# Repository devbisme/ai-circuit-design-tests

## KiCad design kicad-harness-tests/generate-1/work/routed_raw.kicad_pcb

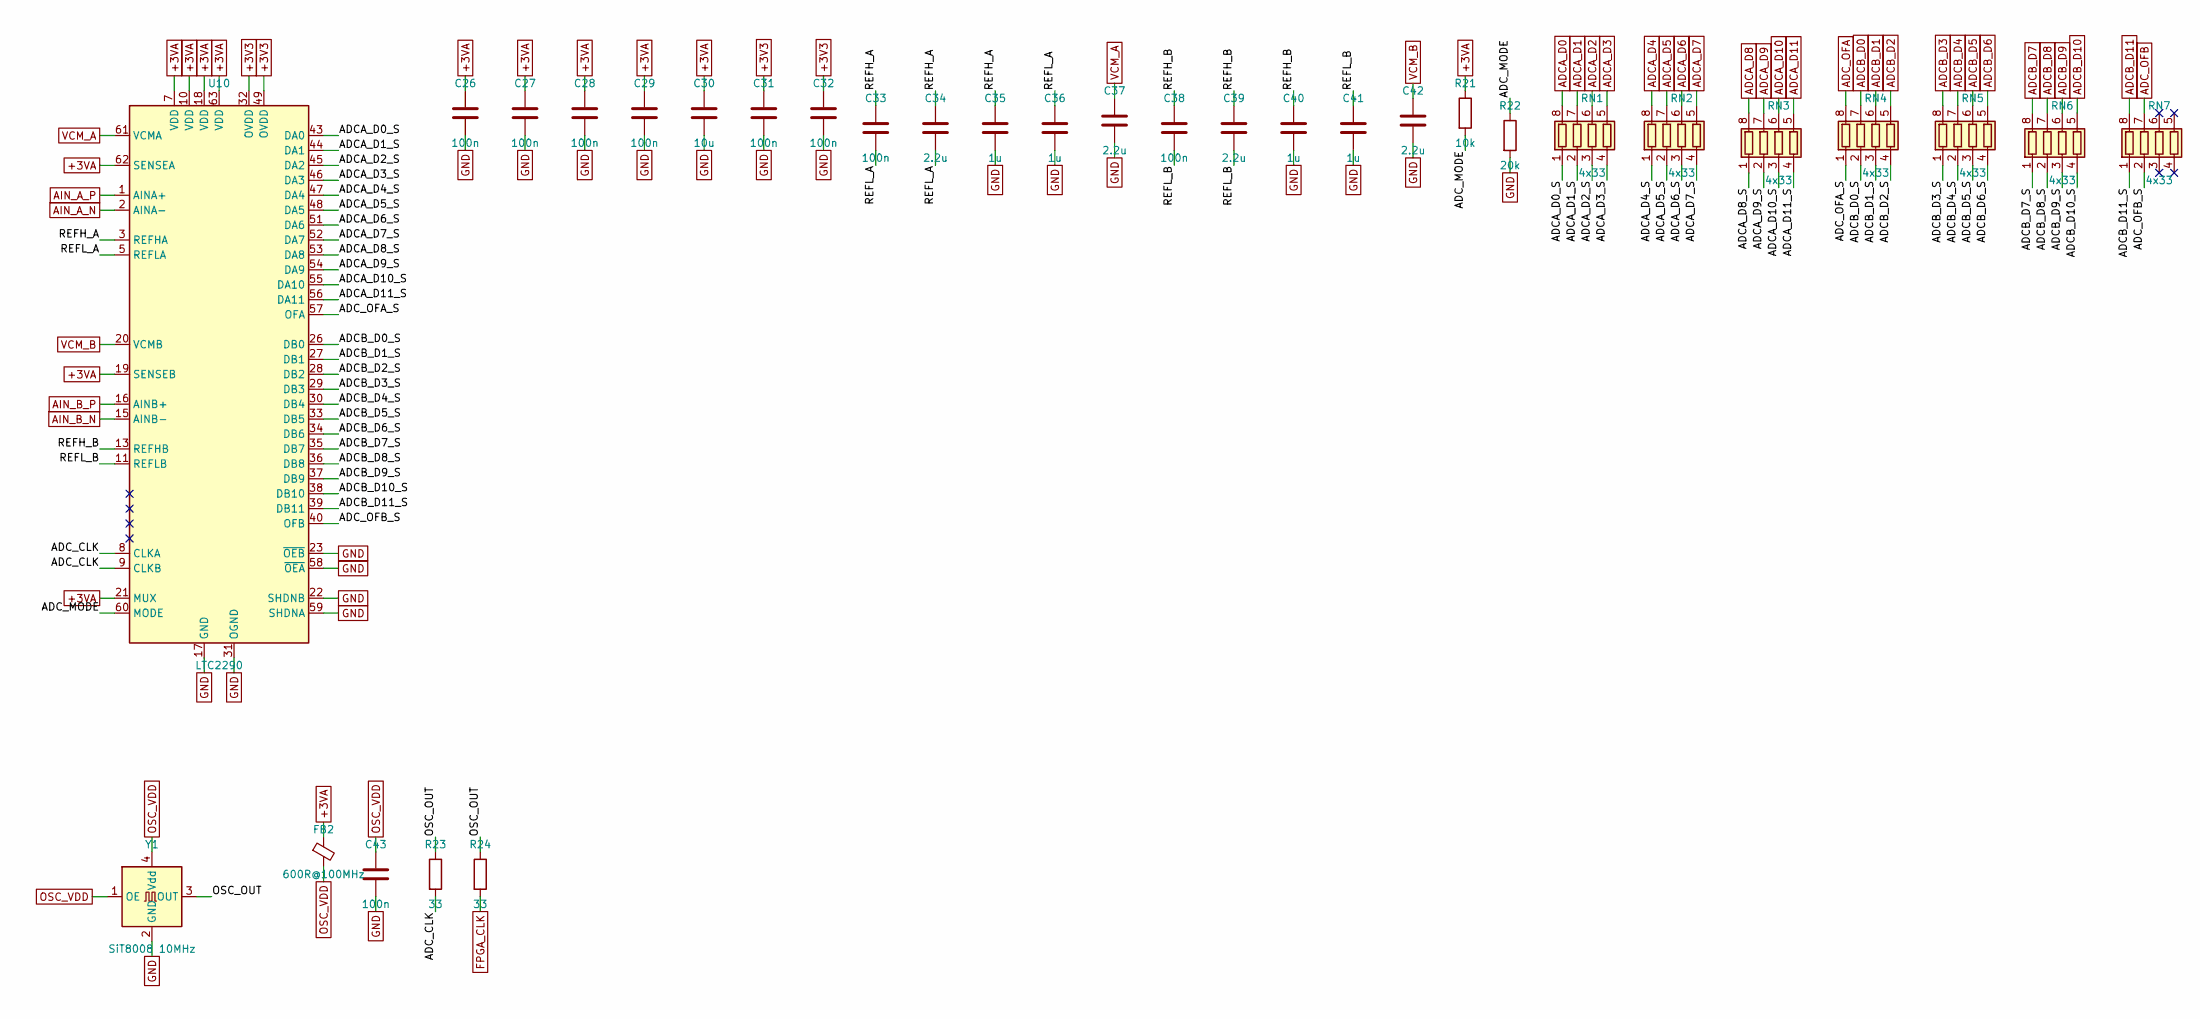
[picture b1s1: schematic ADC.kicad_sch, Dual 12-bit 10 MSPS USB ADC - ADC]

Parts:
C26, C27, C28, C29, C31, C32, C33, C38, C43: 100n; C_0603_1608Metric
C30: 10u; C_0805_2012Metric
C34, C37, C39, C42: 2.2u; C_0603_1608Metric
C35, C36, C40, C41: 1u; C_0603_1608Metric
FB2: 600R@100MHz; L_0805_2012Metric
R21: 10k; R_0603_1608Metric
R22: 20k; R_0603_1608Metric
R23, R24: 33; R_0603_1608Metric
RN1, RN2, RN3, RN4, RN5, RN6, RN7: 4x33; R_Array_Convex_4x0603
U10: LTC2290; QFN-64-1EP_9x9mm_P0.5mm_EP7.15x7.15mm
Y1: SiT8008 10MHz; Oscillator_SMD_SiT_PQFN-4Pin_3.2x2.5mm

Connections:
+3V3: C31.1, C32.1, U10.32 (OVDD), U10.49 (OVDD); also elsewhere on the board
+3VA: C26.1, C27.1, C28.1, C29.1, C30.1, FB2.1, R21.1, U10.7 (VDD), U10.10 (VDD), U10.18 (VDD), U10.19 (SENSEB), U10.21 (MUX), U10.62 (SENSEA), U10.63 (VDD); also elsewhere on the board
/ADC/ADCA_D0_S: RN1.1 (R1.1), U10.43 (DA0)
/ADC/ADCA_D1_S: RN1.2 (R2.1), U10.44 (DA1)
/ADC/ADCA_D2_S: RN1.3 (R3.1), U10.45 (DA2)
/ADC/ADCA_D3_S: RN1.4 (R4.1), U10.46 (DA3)
/ADC/ADCA_D4_S: RN2.1 (R1.1), U10.47 (DA4)
/ADC/ADCA_D5_S: RN2.2 (R2.1), U10.48 (DA5)
/ADC/ADCA_D6_S: RN2.3 (R3.1), U10.51 (DA6)
/ADC/ADCA_D7_S: RN2.4 (R4.1), U10.52 (DA7)
/ADC/ADCA_D8_S: RN3.1 (R1.1), U10.53 (DA8)
/ADC/ADCA_D9_S: RN3.2 (R2.1), U10.54 (DA9)
/ADC/ADCA_D10_S: RN3.3 (R3.1), U10.55 (DA10)
/ADC/ADCA_D11_S: RN3.4 (R4.1), U10.56 (DA11)
/ADC/ADCB_D0_S: RN4.2 (R2.1), U10.26 (DB0)
/ADC/ADCB_D1_S: RN4.3 (R3.1), U10.27 (DB1)
/ADC/ADCB_D2_S: RN4.4 (R4.1), U10.28 (DB2)
/ADC/ADCB_D3_S: RN5.1 (R1.1), U10.29 (DB3)
/ADC/ADCB_D4_S: RN5.2 (R2.1), U10.30 (DB4)
/ADC/ADCB_D5_S: RN5.3 (R3.1), U10.33 (DB5)
/ADC/ADCB_D6_S: RN5.4 (R4.1), U10.34 (DB6)
/ADC/ADCB_D7_S: RN6.1 (R1.1), U10.35 (DB7)
/ADC/ADCB_D8_S: RN6.2 (R2.1), U10.36 (DB8)
/ADC/ADCB_D9_S: RN6.3 (R3.1), U10.37 (DB9)
/ADC/ADCB_D10_S: RN6.4 (R4.1), U10.38 (DB10)
/ADC/ADCB_D11_S: RN7.1 (R1.1), U10.39 (DB11)
/ADC/ADC_CLK: R23.2, U10.8 (CLKA), U10.9 (CLKB)
/ADC/ADC_MODE: R21.2, R22.1, U10.60 (MODE)
/ADC/ADC_OFA_S: RN4.1 (R1.1), U10.57 (OFA)
/ADC/ADC_OFB_S: RN7.2 (R2.1), U10.40 (OFB)
/ADC/OSC_OUT: R23.1, R24.1, Y1.3 (OUT)
/ADC/REFH_A: C33.1, C34.1, C35.1, U10.3 (REFHA), U10.4 (REFHA)
/ADC/REFH_B: C38.1, C39.1, C40.1, U10.13 (REFHB), U10.14 (REFHB)
/ADC/REFL_A: C33.2, C34.2, C36.1, U10.5 (REFLA), U10.6 (REFLA)
/ADC/REFL_B: C38.2, C39.2, C41.1, U10.11 (REFLB), U10.12 (REFLB)
ADCA_D0: RN1.8 (R1.2); also elsewhere on the board
ADCA_D1: RN1.7 (R2.2); also elsewhere on the board
ADCA_D2: RN1.6 (R3.2); also elsewhere on the board
ADCA_D3: RN1.5 (R4.2); also elsewhere on the board
ADCA_D4: RN2.8 (R1.2); also elsewhere on the board
ADCA_D5: RN2.7 (R2.2); also elsewhere on the board
ADCA_D6: RN2.6 (R3.2); also elsewhere on the board
ADCA_D7: RN2.5 (R4.2); also elsewhere on the board
ADCA_D8: RN3.8 (R1.2); also elsewhere on the board
ADCA_D9: RN3.7 (R2.2); also elsewhere on the board
ADCA_D10: RN3.6 (R3.2); also elsewhere on the board
ADCA_D11: RN3.5 (R4.2); also elsewhere on the board
ADCB_D0: RN4.7 (R2.2); also elsewhere on the board
ADCB_D1: RN4.6 (R3.2); also elsewhere on the board
ADCB_D2: RN4.5 (R4.2); also elsewhere on the board
ADCB_D3: RN5.8 (R1.2); also elsewhere on the board
ADCB_D4: RN5.7 (R2.2); also elsewhere on the board
ADCB_D5: RN5.6 (R3.2); also elsewhere on the board
ADCB_D6: RN5.5 (R4.2); also elsewhere on the board
ADCB_D7: RN6.8 (R1.2); also elsewhere on the board
ADCB_D8: RN6.7 (R2.2); also elsewhere on the board
ADCB_D9: RN6.6 (R3.2); also elsewhere on the board
ADCB_D10: RN6.5 (R4.2); also elsewhere on the board
ADCB_D11: RN7.8 (R1.2); also elsewhere on the board
ADC_OFA: RN4.8 (R1.2); also elsewhere on the board
ADC_OFB: RN7.7 (R2.2); also elsewhere on the board
AIN_A_N: U10.2 (AINA-); also elsewhere on the board
AIN_A_P: U10.1 (AINA+); also elsewhere on the board
AIN_B_N: U10.15 (AINB-); also elsewhere on the board
AIN_B_P: U10.16 (AINB+); also elsewhere on the board
FPGA_CLK: R24.2; also elsewhere on the board
GND: C26.2, C27.2, C28.2, C29.2, C30.2, C31.2, C32.2, C35.2, C36.2, C37.2, C40.2, C41.2, C42.2, C43.2, R22.2, U10.17 (GND), U10.22 (SHDNB), U10.23 (~OEB), U10.31 (OGND), U10.50 (OGND), U10.58 (~OEA), U10.59 (SHDNA), U10.64 (GND), U10.65 (GND), Y1.2 (GND); also elsewhere on the board
OSC_VDD: C43.1, FB2.2, Y1.1 (OE), Y1.4 (Vdd)
VCM_A: C37.1, U10.61 (VCMA); also elsewhere on the board
VCM_B: C42.1, U10.20 (VCMB); also elsewhere on the board

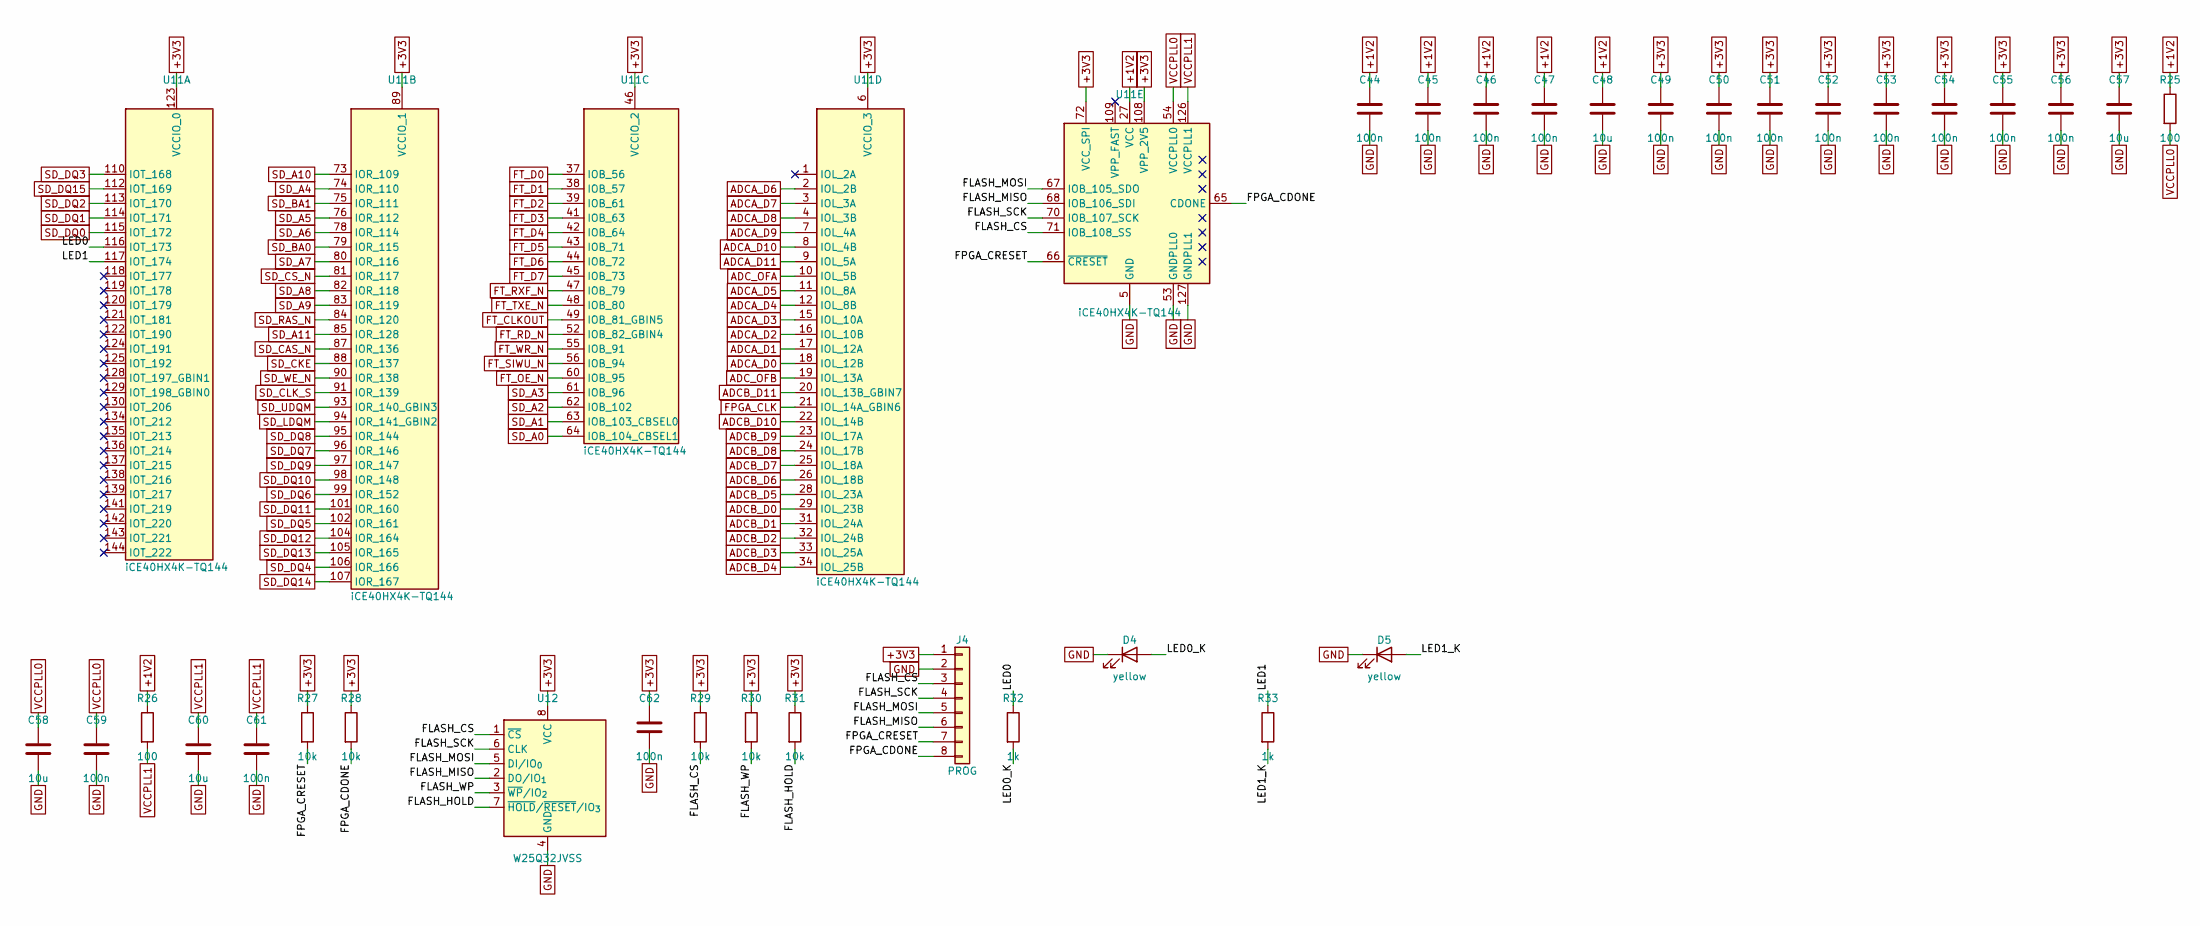
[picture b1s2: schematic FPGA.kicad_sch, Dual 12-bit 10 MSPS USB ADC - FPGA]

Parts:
C44, C45, C46, C47, C49, C50, C51, C52, C53, C54, C55, C56, C59, C61, C62: 100n; C_0603_1608Metric
C48, C57, C58, C60: 10u; C_0805_2012Metric
D4, D5: yellow; LED_0603_1608Metric
J4: PROG; PinHeader_1x08_P2.54mm_Vertical
R25, R26: 100; R_0603_1608Metric
R27, R28, R29, R30, R31: 10k; R_0603_1608Metric
R32, R33: 1k; R_0603_1608Metric
U11: iCE40HX4K-TQ144; TQFP-144_20x20mm_P0.5mm
U12: W25Q32JVSS; SOIC-8_5.3x5.3mm_P1.27mm

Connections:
+1V2: C44.1, C45.1, C46.1, C47.1, C48.1, R25.1, R26.1, U11.27 (VCC), U11.40 (VCC), U11.92 (VCC), U11.111 (VCC); also elsewhere on the board
+3V3: C49.1, C50.1, C51.1, C52.1, C53.1, C54.1, C55.1, C56.1, C57.1, C62.1, J4.1, R27.1, R28.1, R29.1, R30.1, R31.1, U11.6 (VCCIO_3), U11.30 (VCCIO_3), U11.46 (VCCIO_2), U11.57 (VCCIO_2), U11.72 (VCC_SPI), U11.89 (VCCIO_1), U11.100 (VCCIO_1), U11.108 (VPP_2V5), U11.123 (VCCIO_0), U11.131 (VCCIO_0), U12.8 (VCC); also elsewhere on the board
/FPGA/FLASH_CS: J4.3, R29.2, U11.71 (IOB_108_SS), U12.1 (~CS)
/FPGA/FLASH_HOLD: R31.2, U12.7 (~HOLD/~RESET/IO_{3})
/FPGA/FLASH_MISO: J4.6, U11.68 (IOB_106_SDI), U12.2 (DO/IO_{1})
/FPGA/FLASH_MOSI: J4.5, U11.67 (IOB_105_SDO), U12.5 (DI/IO_{0})
/FPGA/FLASH_SCK: J4.4, U11.70 (IOB_107_SCK), U12.6 (CLK)
/FPGA/FLASH_WP: R30.2, U12.3 (~WP/IO_{2})
/FPGA/FPGA_CDONE: J4.8, R28.2, U11.65 (CDONE)
/FPGA/FPGA_CRESET: J4.7, R27.2, U11.66 (~CRESET)
/FPGA/LED0: R32.1, U11.116 (IOT_173)
/FPGA/LED0_K: D4.2 (A), R32.2
/FPGA/LED1: R33.1, U11.117 (IOT_174)
/FPGA/LED1_K: D5.2 (A), R33.2
ADCA_D0: U11.18 (IOL_12B); also elsewhere on the board
ADCA_D1: U11.17 (IOL_12A); also elsewhere on the board
ADCA_D2: U11.16 (IOL_10B); also elsewhere on the board
ADCA_D3: U11.15 (IOL_10A); also elsewhere on the board
ADCA_D4: U11.12 (IOL_8B); also elsewhere on the board
ADCA_D5: U11.11 (IOL_8A); also elsewhere on the board
ADCA_D6: U11.2 (IOL_2B); also elsewhere on the board
ADCA_D7: U11.3 (IOL_3A); also elsewhere on the board
ADCA_D8: U11.4 (IOL_3B); also elsewhere on the board
ADCA_D9: U11.7 (IOL_4A); also elsewhere on the board
ADCA_D10: U11.8 (IOL_4B); also elsewhere on the board
ADCA_D11: U11.9 (IOL_5A); also elsewhere on the board
ADCB_D0: U11.29 (IOL_23B); also elsewhere on the board
ADCB_D1: U11.31 (IOL_24A); also elsewhere on the board
ADCB_D2: U11.32 (IOL_24B); also elsewhere on the board
ADCB_D3: U11.33 (IOL_25A); also elsewhere on the board
ADCB_D4: U11.34 (IOL_25B); also elsewhere on the board
ADCB_D5: U11.28 (IOL_23A); also elsewhere on the board
ADCB_D6: U11.26 (IOL_18B); also elsewhere on the board
ADCB_D7: U11.25 (IOL_18A); also elsewhere on the board
ADCB_D8: U11.24 (IOL_17B); also elsewhere on the board
ADCB_D9: U11.23 (IOL_17A); also elsewhere on the board
ADCB_D10: U11.22 (IOL_14B); also elsewhere on the board
ADCB_D11: U11.20 (IOL_13B_GBIN7); also elsewhere on the board
ADC_OFA: U11.10 (IOL_5B); also elsewhere on the board
ADC_OFB: U11.19 (IOL_13A); also elsewhere on the board
FPGA_CLK: U11.21 (IOL_14A_GBIN6); also elsewhere on the board
FT_CLKOUT: U11.49 (IOB_81_GBIN5); also elsewhere on the board
FT_D0: U11.37 (IOB_56); also elsewhere on the board
FT_D1: U11.38 (IOB_57); also elsewhere on the board
FT_D2: U11.39 (IOB_61); also elsewhere on the board
FT_D3: U11.41 (IOB_63); also elsewhere on the board
FT_D4: U11.42 (IOB_64); also elsewhere on the board
FT_D5: U11.43 (IOB_71); also elsewhere on the board
FT_D6: U11.44 (IOB_72); also elsewhere on the board
FT_D7: U11.45 (IOB_73); also elsewhere on the board
FT_OE_N: U11.60 (IOB_95); also elsewhere on the board
FT_RD_N: U11.52 (IOB_82_GBIN4); also elsewhere on the board
FT_RXF_N: U11.47 (IOB_79); also elsewhere on the board
FT_SIWU_N: U11.56 (IOB_94); also elsewhere on the board
FT_TXE_N: U11.48 (IOB_80); also elsewhere on the board
FT_WR_N: U11.55 (IOB_91); also elsewhere on the board
GND: C44.2, C45.2, C46.2, C47.2, C48.2, C49.2, C50.2, C51.2, C52.2, C53.2, C54.2, C55.2, C56.2, C57.2, C58.2, C59.2, C60.2, C61.2, C62.2, D4.1 (K), D5.1 (K), J4.2, U11.5 (GND), U11.13 (GND), U11.14 (GND), U11.53 (GNDPLL0), U11.59 (GND), U11.69 (GND), U11.86 (GND), U11.103 (GND), U11.127 (GNDPLL1), U11.132 (GND), U11.140 (GND), U12.4 (GND); also elsewhere on the board
SD_A0: U11.64 (IOB_104_CBSEL1); also elsewhere on the board
SD_A1: U11.63 (IOB_103_CBSEL0); also elsewhere on the board
SD_A2: U11.62 (IOB_102); also elsewhere on the board
SD_A3: U11.61 (IOB_96); also elsewhere on the board
SD_A4: U11.74 (IOR_110); also elsewhere on the board
SD_A5: U11.76 (IOR_112); also elsewhere on the board
SD_A6: U11.78 (IOR_114); also elsewhere on the board
SD_A7: U11.80 (IOR_116); also elsewhere on the board
SD_A8: U11.82 (IOR_118); also elsewhere on the board
SD_A9: U11.83 (IOR_119); also elsewhere on the board
SD_A10: U11.73 (IOR_109); also elsewhere on the board
SD_A11: U11.85 (IOR_128); also elsewhere on the board
SD_BA0: U11.79 (IOR_115); also elsewhere on the board
SD_BA1: U11.75 (IOR_111); also elsewhere on the board
SD_CAS_N: U11.87 (IOR_136); also elsewhere on the board
SD_CKE: U11.88 (IOR_137); also elsewhere on the board
SD_CLK_S: U11.91 (IOR_139); also elsewhere on the board
SD_CS_N: U11.81 (IOR_117); also elsewhere on the board
SD_DQ0: U11.115 (IOT_172); also elsewhere on the board
SD_DQ1: U11.114 (IOT_171); also elsewhere on the board
SD_DQ2: U11.113 (IOT_170); also elsewhere on the board
SD_DQ3: U11.110 (IOT_168); also elsewhere on the board
SD_DQ4: U11.106 (IOR_166); also elsewhere on the board
SD_DQ5: U11.102 (IOR_161); also elsewhere on the board
SD_DQ6: U11.99 (IOR_152); also elsewhere on the board
SD_DQ7: U11.96 (IOR_146); also elsewhere on the board
SD_DQ8: U11.95 (IOR_144); also elsewhere on the board
SD_DQ9: U11.97 (IOR_147); also elsewhere on the board
SD_DQ10: U11.98 (IOR_148); also elsewhere on the board
SD_DQ11: U11.101 (IOR_160); also elsewhere on the board
SD_DQ12: U11.104 (IOR_164); also elsewhere on the board
SD_DQ13: U11.105 (IOR_165); also elsewhere on the board
SD_DQ14: U11.107 (IOR_167); also elsewhere on the board
SD_DQ15: U11.112 (IOT_169); also elsewhere on the board
SD_LDQM: U11.94 (IOR_141_GBIN2); also elsewhere on the board
SD_RAS_N: U11.84 (IOR_120); also elsewhere on the board
SD_UDQM: U11.93 (IOR_140_GBIN3); also elsewhere on the board
SD_WE_N: U11.90 (IOR_138); also elsewhere on the board
VCCPLL0: C58.1, C59.1, R25.2, U11.54 (VCCPLL0)
VCCPLL1: C60.1, C61.1, R26.2, U11.126 (VCCPLL1)

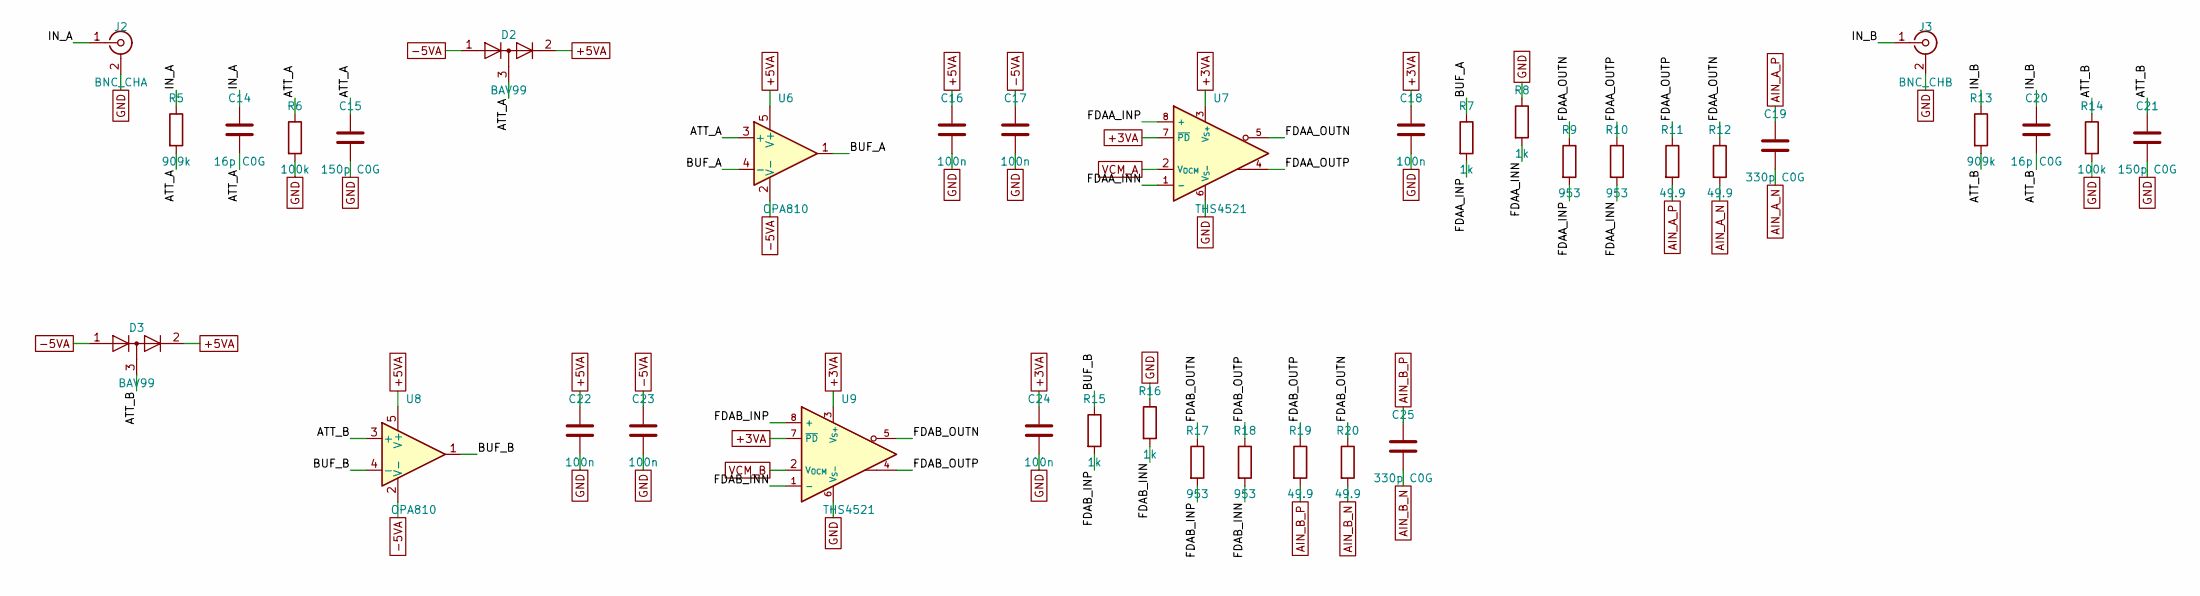
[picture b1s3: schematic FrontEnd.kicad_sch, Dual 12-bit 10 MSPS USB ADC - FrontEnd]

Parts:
C14, C20: 16p C0G; C_1206_3216Metric
C15, C21: 150p C0G; C_0603_1608Metric
C16, C17, C18, C22, C23, C24: 100n; C_0603_1608Metric
C19, C25: 330p C0G; C_0603_1608Metric
D2, D3: BAV99; SOT-23
J2: BNC_CHA; BNC_Amphenol_B6252HB-NPP3G-50_Horizontal
J3: BNC_CHB; BNC_Amphenol_B6252HB-NPP3G-50_Horizontal
R5, R13: 909k; R_1206_3216Metric
R6, R14: 100k; R_0603_1608Metric
R7, R8, R15, R16: 1k; R_0603_1608Metric
R9, R10, R17, R18: 953; R_0603_1608Metric
R11, R12, R19, R20: 49.9; R_0603_1608Metric
U6, U8: OPA810; SOT-23-5
U7, U9: THS4521; SOIC-8_3.9x4.9mm_P1.27mm

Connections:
+3VA: C18.1, C24.1, U7.3 (V_{S+}), U7.7 (~PD), U9.3 (V_{S+}), U9.7 (~PD); also elsewhere on the board
+5VA: C16.1, C22.1, D2.2 (A), D3.2 (A), U6.5 (V+), U8.5 (V+); also elsewhere on the board
-5VA: C17.1, C23.1, D2.1 (K), D3.1 (K), U6.2 (V-), U8.2 (V-); also elsewhere on the board
/FrontEnd/ATT_A: C14.2, C15.1, D2.3 (K), R5.2, R6.1, U6.3 (+)
/FrontEnd/ATT_B: C20.2, C21.1, D3.3 (K), R13.2, R14.1, U8.3 (+)
/FrontEnd/BUF_A: R7.1, U6.1, U6.4 (-)
/FrontEnd/BUF_B: R15.1, U8.1, U8.4 (-)
/FrontEnd/FDAA_INN: R8.2, R10.2, U7.1 (-)
/FrontEnd/FDAA_INP: R7.2, R9.2, U7.8 (+)
/FrontEnd/FDAA_OUTN: R9.1, R12.1, U7.5
/FrontEnd/FDAA_OUTP: R10.1, R11.1, U7.4
/FrontEnd/FDAB_INN: R16.2, R18.2, U9.1 (-)
/FrontEnd/FDAB_INP: R15.2, R17.2, U9.8 (+)
/FrontEnd/FDAB_OUTN: R17.1, R20.1, U9.5
/FrontEnd/FDAB_OUTP: R18.1, R19.1, U9.4
/FrontEnd/IN_A: C14.1, J2.1 (In), R5.1
/FrontEnd/IN_B: C20.1, J3.1 (In), R13.1
AIN_A_N: C19.2, R12.2; also elsewhere on the board
AIN_A_P: C19.1, R11.2; also elsewhere on the board
AIN_B_N: C25.2, R20.2; also elsewhere on the board
AIN_B_P: C25.1, R19.2; also elsewhere on the board
GND: C15.2, C16.2, C17.2, C18.2, C21.2, C22.2, C23.2, C24.2, J2.2 (Ext), J3.2 (Ext), R6.2, R8.1, R14.2, R16.1, U7.6 (V_{S-}), U9.6 (V_{S-}); also elsewhere on the board
VCM_A: U7.2 (V_{OCM}); also elsewhere on the board
VCM_B: U9.2 (V_{OCM}); also elsewhere on the board

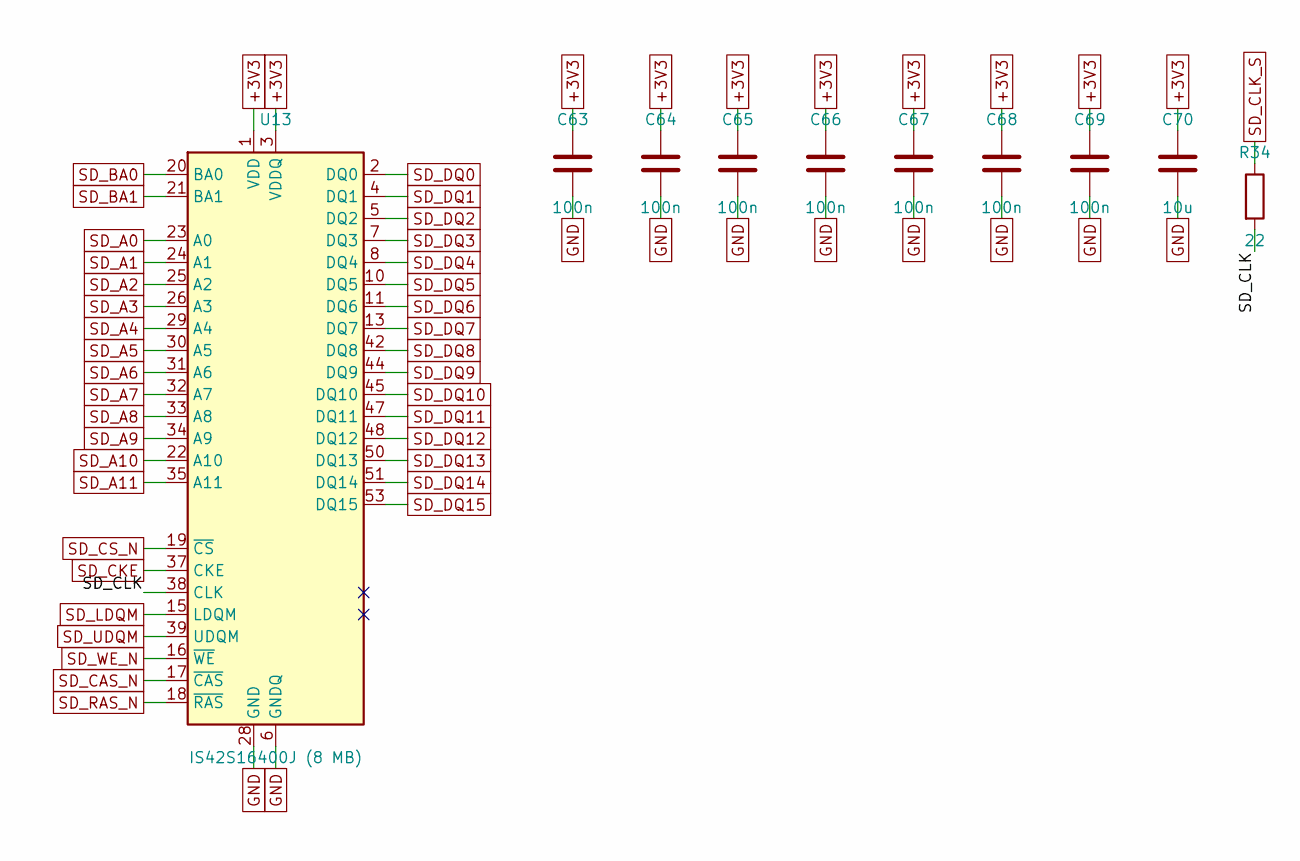
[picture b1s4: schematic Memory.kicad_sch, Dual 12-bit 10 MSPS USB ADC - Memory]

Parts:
C63, C64, C65, C66, C67, C68, C69: 100n; C_0603_1608Metric
C70: 10u; C_0805_2012Metric
R34: 22; R_0603_1608Metric
U13: IS42S16400J (8 MB); TSOP-II-54_22.2x10.16mm_P0.8mm

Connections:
+3V3: C63.1, C64.1, C65.1, C66.1, C67.1, C68.1, C69.1, C70.1, U13.1 (VDD), U13.3 (VDDQ), U13.9 (VDDQ), U13.14 (VDD), U13.27 (VDD), U13.43 (VDDQ), U13.49 (VDDQ); also elsewhere on the board
/Memory/SD_CLK: R34.2, U13.38 (CLK)
GND: C63.2, C64.2, C65.2, C66.2, C67.2, C68.2, C69.2, C70.2, U13.6 (GNDQ), U13.12 (GNDQ), U13.28 (GND), U13.41 (GND), U13.46 (GNDQ), U13.52 (GNDQ), U13.54 (GND); also elsewhere on the board
SD_A0: U13.23 (A0); also elsewhere on the board
SD_A1: U13.24 (A1); also elsewhere on the board
SD_A2: U13.25 (A2); also elsewhere on the board
SD_A3: U13.26 (A3); also elsewhere on the board
SD_A4: U13.29 (A4); also elsewhere on the board
SD_A5: U13.30 (A5); also elsewhere on the board
SD_A6: U13.31 (A6); also elsewhere on the board
SD_A7: U13.32 (A7); also elsewhere on the board
SD_A8: U13.33 (A8); also elsewhere on the board
SD_A9: U13.34 (A9); also elsewhere on the board
SD_A10: U13.22 (A10); also elsewhere on the board
SD_A11: U13.35 (A11); also elsewhere on the board
SD_BA0: U13.20 (BA0); also elsewhere on the board
SD_BA1: U13.21 (BA1); also elsewhere on the board
SD_CAS_N: U13.17 (~CAS); also elsewhere on the board
SD_CKE: U13.37 (CKE); also elsewhere on the board
SD_CLK_S: R34.1; also elsewhere on the board
SD_CS_N: U13.19 (~CS); also elsewhere on the board
SD_DQ0: U13.2 (DQ0); also elsewhere on the board
SD_DQ1: U13.4 (DQ1); also elsewhere on the board
SD_DQ2: U13.5 (DQ2); also elsewhere on the board
SD_DQ3: U13.7 (DQ3); also elsewhere on the board
SD_DQ4: U13.8 (DQ4); also elsewhere on the board
SD_DQ5: U13.10 (DQ5); also elsewhere on the board
SD_DQ6: U13.11 (DQ6); also elsewhere on the board
SD_DQ7: U13.13 (DQ7); also elsewhere on the board
SD_DQ8: U13.42 (DQ8); also elsewhere on the board
SD_DQ9: U13.44 (DQ9); also elsewhere on the board
SD_DQ10: U13.45 (DQ10); also elsewhere on the board
SD_DQ11: U13.47 (DQ11); also elsewhere on the board
SD_DQ12: U13.48 (DQ12); also elsewhere on the board
SD_DQ13: U13.50 (DQ13); also elsewhere on the board
SD_DQ14: U13.51 (DQ14); also elsewhere on the board
SD_DQ15: U13.53 (DQ15); also elsewhere on the board
SD_LDQM: U13.15 (LDQM); also elsewhere on the board
SD_RAS_N: U13.18 (~RAS); also elsewhere on the board
SD_UDQM: U13.39 (UDQM); also elsewhere on the board
SD_WE_N: U13.16 (~WE); also elsewhere on the board

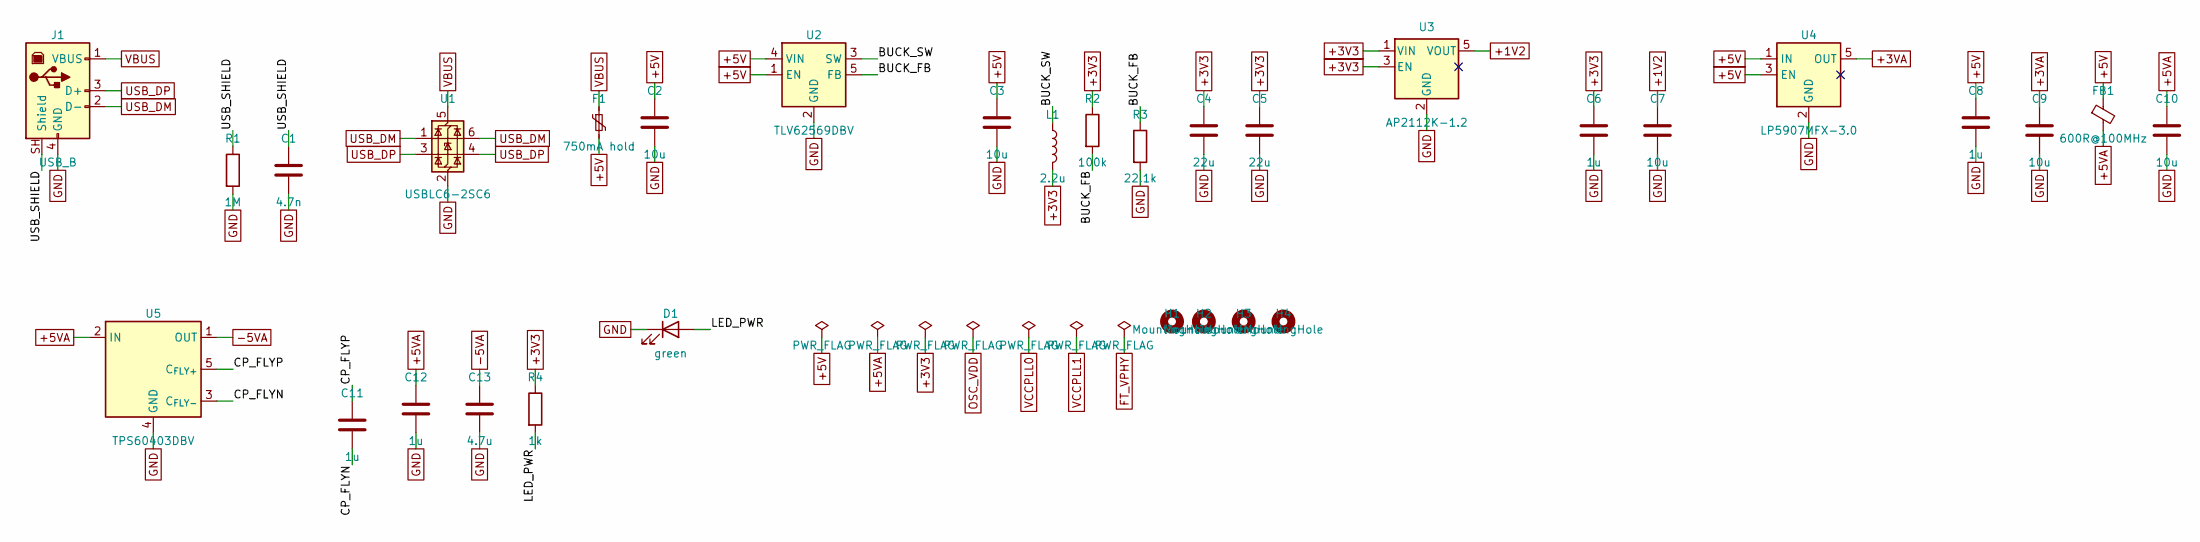
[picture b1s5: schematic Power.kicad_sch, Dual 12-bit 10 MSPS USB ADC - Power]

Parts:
C1: 4.7n; C_0805_2012Metric
C2, C3, C7, C9, C10: 10u; C_0805_2012Metric
C4, C5: 22u; C_0805_2012Metric
C6, C8, C11, C12: 1u; C_0603_1608Metric
C13: 4.7u; C_0805_2012Metric
D1: green; LED_0603_1608Metric
F1: 750mA hold; Fuse_1206_3216Metric
FB1: 600R@100MHz; L_0805_2012Metric
H1, H2, H3, H4: MountingHole; MountingHole_3.2mm_M3
J1: USB_B; USB_B_OST_USB-B1HSxx_Horizontal
L1: 2.2u; L_Bourns-SRN4018
R1: 1M; R_0603_1608Metric
R2: 100k; R_0603_1608Metric
R3: 22.1k; R_0603_1608Metric
R4: 1k; R_0603_1608Metric
U1: USBLC6-2SC6; SOT-23-6
U2: TLV62569DBV; SOT-23-5
U3: AP2112K-1.2; SOT-23-5
U4: LP5907MFX-3.0; SOT-23-5
U5: TPS60403DBV; SOT-23-5

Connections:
+1V2: C7.1, U3.5 (VOUT); also elsewhere on the board
+3V3: C4.1, C5.1, C6.1, L1.2, R2.1, R4.1, U3.1 (VIN), U3.3 (EN); also elsewhere on the board
+3VA: C9.1, U4.5 (OUT); also elsewhere on the board
+5V: C2.1, C3.1, C8.1, F1.2, FB1.1, U2.1 (EN), U2.4 (VIN), U4.1 (IN), U4.3 (EN)
+5VA: C10.1, C12.1, FB1.2, U5.2 (IN); also elsewhere on the board
-5VA: C13.1, U5.1 (OUT); also elsewhere on the board
/Power/BUCK_FB: R2.2, R3.1, U2.5 (FB)
/Power/BUCK_SW: L1.1, U2.3 (SW)
/Power/CP_FLYN: C11.2, U5.3 (C_{FLY-})
/Power/CP_FLYP: C11.1, U5.5 (C_{FLY+})
/Power/LED_PWR: D1.2 (A), R4.2
/Power/USB_SHIELD: C1.1, J1.SH (Shield), R1.1
GND: C1.2, C2.2, C3.2, C4.2, C5.2, C6.2, C7.2, C8.2, C9.2, C10.2, C12.2, C13.2, D1.1 (K), J1.4 (GND), R1.2, R3.2, U1.2 (GND), U2.2 (GND), U3.2 (GND), U4.2 (GND), U5.4 (GND); also elsewhere on the board
USB_DM: J1.2 (D-), U1.1 (I/O1), U1.6 (I/O1); also elsewhere on the board
USB_DP: J1.3 (D+), U1.3 (I/O2), U1.4 (I/O2); also elsewhere on the board
VBUS: F1.1, J1.1 (VBUS), U1.5 (VBUS)

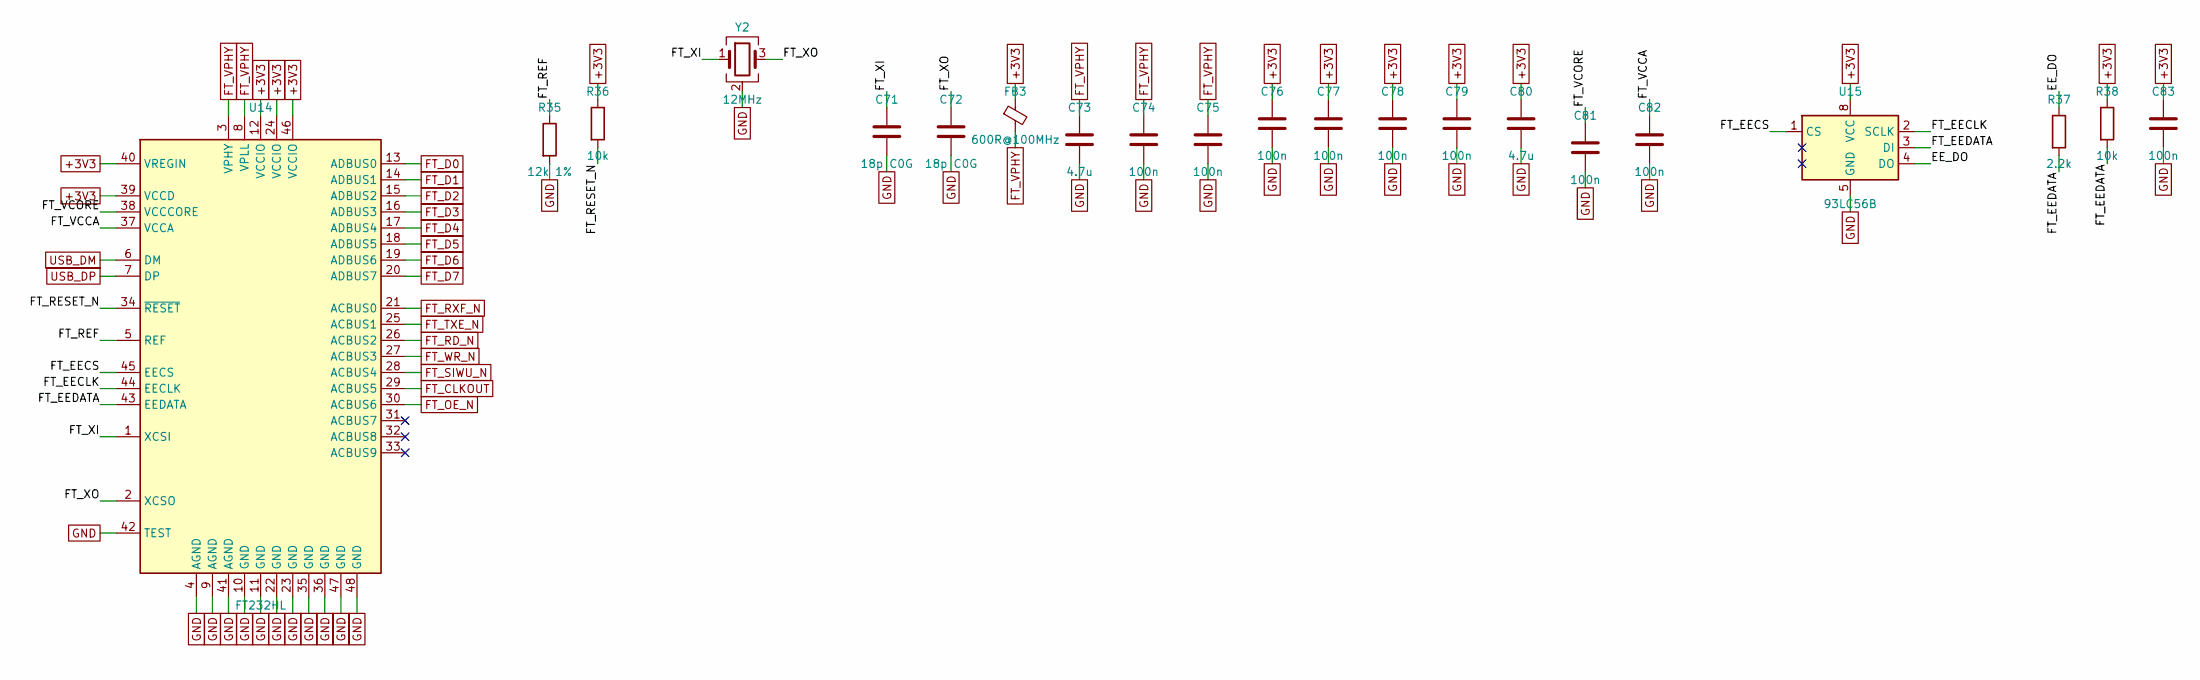
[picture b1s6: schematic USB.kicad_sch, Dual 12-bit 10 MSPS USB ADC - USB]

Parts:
C71, C72: 18p C0G; C_0603_1608Metric
C73, C80: 4.7u; C_0805_2012Metric
C74, C75, C76, C77, C78, C79, C81, C82, C83: 100n; C_0603_1608Metric
FB3: 600R@100MHz; L_0805_2012Metric
R35: 12k 1%; R_0603_1608Metric
R36, R38: 10k; R_0603_1608Metric
R37: 2.2k; R_0603_1608Metric
U14: FT232HL; LQFP-48_7x7mm_P0.5mm
U15: 93LC56B; SOIC-8_3.9x4.9mm_P1.27mm
Y2: 12MHz; Crystal_SMD_3225-4Pin_3.2x2.5mm

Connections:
+3V3: C76.1, C77.1, C78.1, C79.1, C80.1, C83.1, FB3.1, R36.1, R38.1, U14.12 (VCCIO), U14.24 (VCCIO), U14.39 (VCCD), U14.40 (VREGIN), U14.46 (VCCIO), U15.8 (VCC); also elsewhere on the board
/USB/EE_DO: R37.1, U15.4 (DO)
/USB/FT_EECLK: U14.44 (EECLK), U15.2 (SCLK)
/USB/FT_EECS: U14.45 (EECS), U15.1 (CS)
/USB/FT_EEDATA: R37.2, R38.2, U14.43 (EEDATA), U15.3 (DI)
/USB/FT_REF: R35.1, U14.5 (REF)
/USB/FT_RESET_N: R36.2, U14.34 (~RESET)
/USB/FT_VCCA: C82.1, U14.37 (VCCA)
/USB/FT_VCORE: C81.1, U14.38 (VCCCORE)
/USB/FT_XI: C71.1, U14.1 (XCSI), Y2.1
/USB/FT_XO: C72.1, U14.2 (XCSO), Y2.3
FT_CLKOUT: U14.29 (ACBUS5); also elsewhere on the board
FT_D0: U14.13 (ADBUS0); also elsewhere on the board
FT_D1: U14.14 (ADBUS1); also elsewhere on the board
FT_D2: U14.15 (ADBUS2); also elsewhere on the board
FT_D3: U14.16 (ADBUS3); also elsewhere on the board
FT_D4: U14.17 (ADBUS4); also elsewhere on the board
FT_D5: U14.18 (ADBUS5); also elsewhere on the board
FT_D6: U14.19 (ADBUS6); also elsewhere on the board
FT_D7: U14.20 (ADBUS7); also elsewhere on the board
FT_OE_N: U14.30 (ACBUS6); also elsewhere on the board
FT_RD_N: U14.26 (ACBUS2); also elsewhere on the board
FT_RXF_N: U14.21 (ACBUS0); also elsewhere on the board
FT_SIWU_N: U14.28 (ACBUS4); also elsewhere on the board
FT_TXE_N: U14.25 (ACBUS1); also elsewhere on the board
FT_VPHY: C73.1, C74.1, C75.1, FB3.2, U14.3 (VPHY), U14.8 (VPLL)
FT_WR_N: U14.27 (ACBUS3); also elsewhere on the board
GND: C71.2, C72.2, C73.2, C74.2, C75.2, C76.2, C77.2, C78.2, C79.2, C80.2, C81.2, C82.2, C83.2, R35.2, U14.4 (AGND), U14.9 (AGND), U14.10 (GND), U14.11 (GND), U14.22 (GND), U14.23 (GND), U14.35 (GND), U14.36 (GND), U14.41 (AGND), U14.42 (TEST), U14.47 (GND), U14.48 (GND), U15.5 (GND), Y2.2 (G), Y2.4 (G); also elsewhere on the board
USB_DM: U14.6 (DM); also elsewhere on the board
USB_DP: U14.7 (DP); also elsewhere on the board

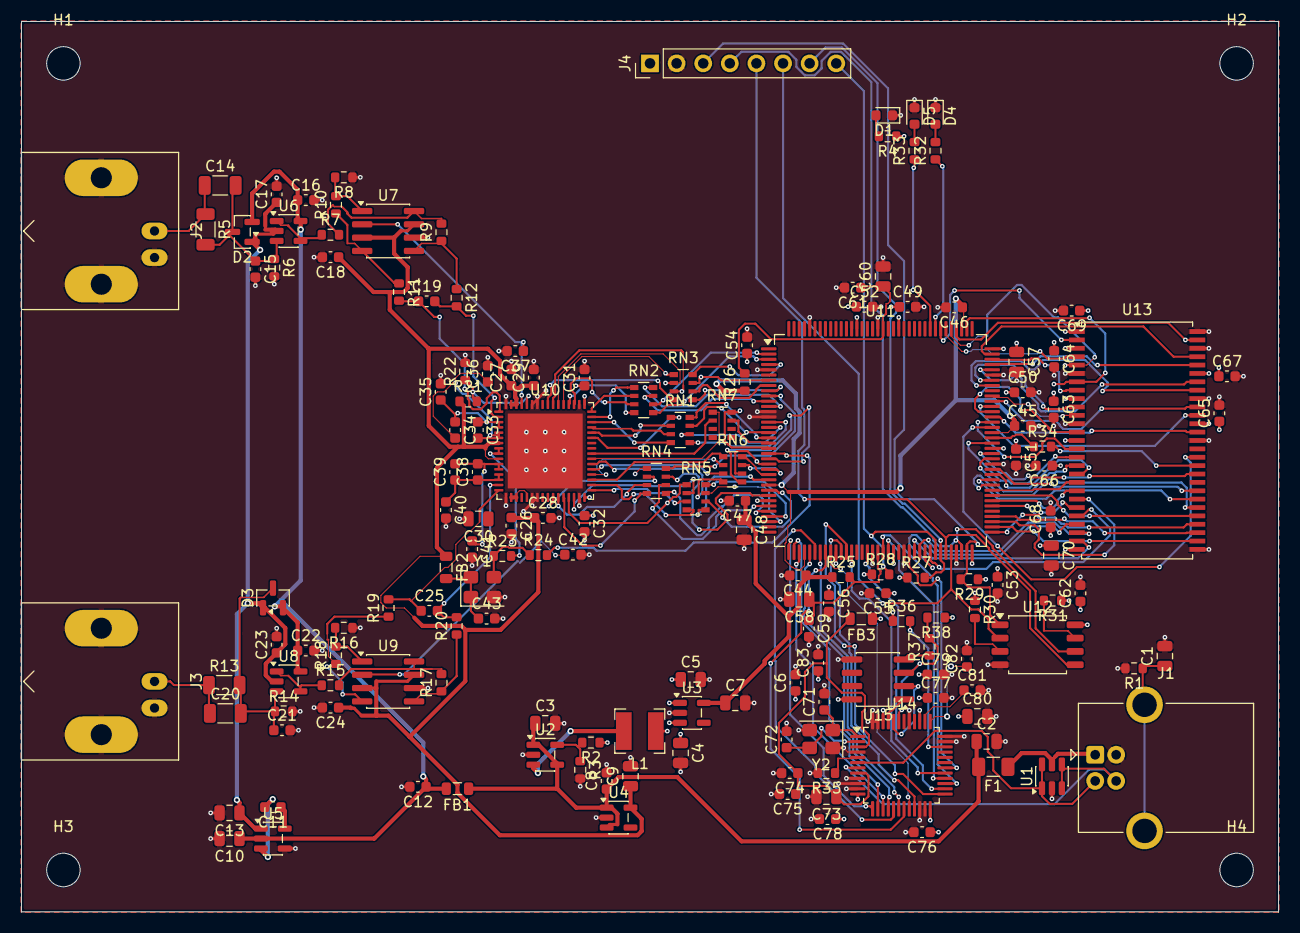
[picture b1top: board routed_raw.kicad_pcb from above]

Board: 4 copper layers, 120.0 x 85.0 mm, 163 parts (0 on the bottom side), 176 nets.
